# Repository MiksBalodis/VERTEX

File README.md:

# VERTEX Flight Computer

Avionics system for actively controlled high-power rockets: an STM32 flight computer that estimates vehicle state in real time and drives control actuators, plus a ground station for receiving, storing and analysing flight data.

**Authors:** Miks Balodis, Aleksandrs Jesiļevskis

---

## Overview

The system covers the full avionics chain:

- **Flight computer** – sensor acquisition, state estimation, active control and flight data logging
- **Telemetry link** – LoRa downlink to the ground during flight
- **Ground station** – receiver hardware and a desktop GUI for live visualisation and data export

The flight computer can:

- estimate the rocket's attitude, velocity and altitude in real time,
- drive up to **4 PWM actuator channels** (servo-actuated control fins or a TVC gimbal),
- log flight data on board for post-flight analysis,
- stream telemetry to the ground station during flight.

## What is active control?

Active control continuously:

1. measures the vehicle's state (orientation, angular rates, velocity),
2. computes the required correction,
3. commands the actuators via PWM.

Unlike passive stabilisation, which relies on fixed aerodynamic surfaces, an active system can respond to disturbances such as wind gusts, thrust misalignment and asymmetries during flight.

## Architecture

## Hardware

| Function | Component | Notes |
|---|---|---|
| MCU | STM32F405RGT6 | Cortex-M4F, FPU + DSP, DMA for peripheral transfers |
| Barometer | BMP388 | Altitude estimation; SPI up to 10 MHz |
| IMU | LSM6DSO | 3-axis accelerometer + gyroscope|
| GNSS | u-blox MAX-M10S | ~1.5 m CEP position accuracy, high altitude capable |
| Flight data storage | SPI NOR flash | Exposed to a PC as a USB Mass Storage device |
| Configuration storage | 24LC64 EEPROM | Persistent parameters, separate from flight logs |
| Telemetry | EBYTE E22-400M22S | LoRa operating at 433 MHz |
| Actuators | 4× PWM outputs | Servo driven fins or TVC gimbal |

Flight logs and configuration are deliberately kept on separate memories: the EEPROM is simple to access and keeps configuration safe from being overwritten by logging.

## Software

- **Firmware:** C/C++ on STM32 (STM32CubeIDE / STM32Cube HAL), DMA-driven sensor I/O
- **State estimation:** Kalman filter
- **Control:** PID controller
- **Simulation & tuning:** MATLAB/Simulink for controller and filter design; RocketPy for flight trajectory simulation
- **Ground station GUI:** JavaScript + Svelte, with real time plots and data export
- **PCB design:** KiCad

## Intended users

- student and university rocketry teams
- embedded systems and control algorithm developers
- experimental rocketry and UAV hobbyists

## Deliverables

- Flight computer PCB
- Flight firmware
- Ground station hardware and GUI
- Documentation

## License

All materials in this repository are free to use. Attribution is not required, but a short mention of where they came from is appreciated.

## Contact

For questions, contact Miks Balodis.

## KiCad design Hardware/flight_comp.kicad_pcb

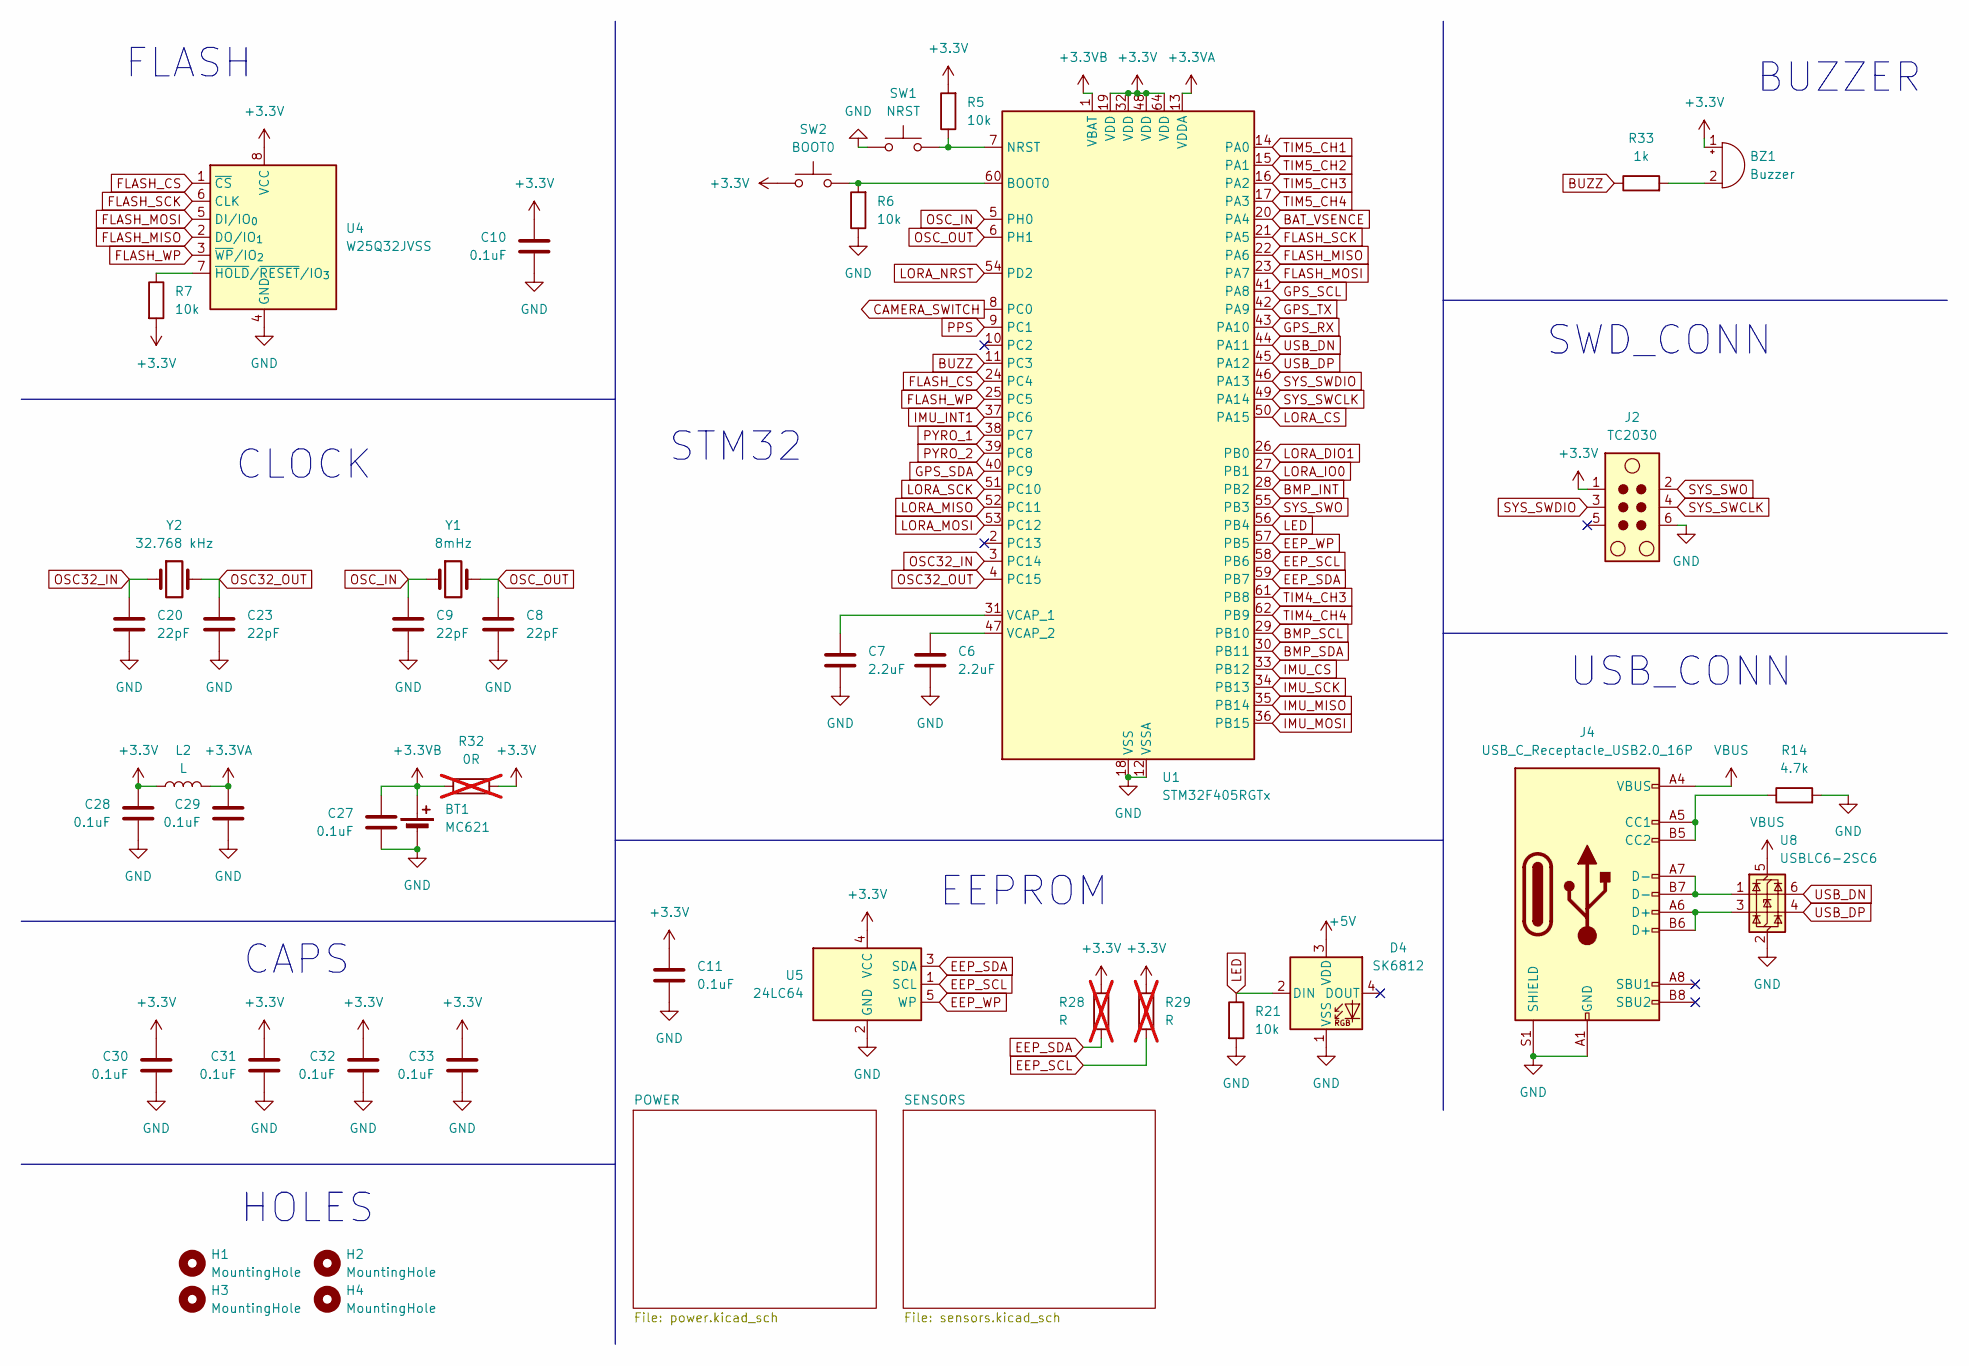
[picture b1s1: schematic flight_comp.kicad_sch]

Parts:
BT1: MC621; BatteryHolder_Keystone_2998_1x6.8mm
BZ1: Buzzer; Buzzer_CUI_CPT-9019S-SMT
C6, C7: 2.2uF; C_0603_1608Metric
C8, C9: 22pF; C_0603_1608Metric
C10, C11, C27, C28, C29, C30, C31, C32, C33: 0.1uF; C_0603_1608Metric
C20, C23: 22pF; C_0402_1005Metric
D4: SK6812; LED_SK6812_PLCC4_5.0x5.0mm_P3.2mm
H1, H2, H3, H4: MountingHole; MountingHole_3.2mm_M3
J2: TC2030; Tag-Connect_TC2030-IDC-NL_2x03_P1.27mm_Vertical
J4: USB_C_Receptacle_USB2.0_16P; USB_C_Receptacle_GCT_USB4110
L2: L; L_0603_1608Metric
R5, R6, R7, R21: 10k; R_0603_1608Metric
R14: 4.7k; R_0603_1608Metric
R28, R29: R; R_0603_1608Metric; not fitted
R32: 0R; R_0603_1608Metric; not fitted
R33: 1k; R_0603_1608Metric
SW1: NRST; SW_SPST_CK_RS282G05A3
SW2: BOOT0; SW_SPST_CK_RS282G05A3
U1: STM32F405RGTx; LQFP-64_10x10mm_P0.5mm
U4: W25Q32JVSS; SOIC-8_5.3x5.3mm_P1.27mm
U5: 24LC64; SOT-23-5
U8: USBLC6-2SC6; SOT-23-6
Y1: 8mHz; Crystal_SMD_5032-2Pin_5.0x3.2mm
Y2: 32.768 kHz; Crystal_SMD_3215-2Pin_3.2x1.5mm

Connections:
+3.3V: BZ1.1 (+), C10.1, C11.1, C28.1, C30.1, C31.1, C32.1, C33.1, J2.1, L2.1, R5.2, R7.2, R28.1, R29.1, R32.2, SW2.1, U1.19 (VDD), U1.32 (VDD), U1.48 (VDD), U1.64 (VDD), U4.8 (VCC), U5.4 (VCC); also elsewhere on the board
+3.3VA: C29.1, L2.2, U1.13 (VDDA)
+3.3VB: BT1.1 (+), C27.1, R32.1, U1.1 (VBAT)
+5V: D4.3 (VDD); also elsewhere on the board
BAT_VSENCE: U1.20 (PA4); also elsewhere on the board
BMP_INT: U1.28 (PB2); also elsewhere on the board
BMP_SCL: U1.29 (PB10); also elsewhere on the board
BMP_SDA: U1.30 (PB11); also elsewhere on the board
BUZZ: R33.1, U1.11 (PC3)
CAMERA_SWITCH: U1.8 (PC0); also elsewhere on the board
EEP_SCL: R29.2, U1.58 (PB6), U5.1 (SCL)
EEP_SDA: R28.2, U1.59 (PB7), U5.3 (SDA)
EEP_WP: U1.57 (PB5), U5.5 (WP)
FLASH_CS: U1.24 (PC4), U4.1 (~CS)
FLASH_MISO: U1.22 (PA6), U4.2 (DO/IO_{1})
FLASH_MOSI: U1.23 (PA7), U4.5 (DI/IO_{0})
FLASH_SCK: U1.21 (PA5), U4.6 (CLK)
FLASH_WP: U1.25 (PC5), U4.3 (~WP/IO_{2})
GND: BT1.2 (-), C6.2, C7.2, C8.2, C9.2, C10.2, C11.2, C20.2, C23.2, C27.2, C28.2, C29.2, C30.2, C31.2, C32.2, C33.2, D4.1 (VSS), J2.6, J4.A1 (GND), J4.A12 (GND), J4.B1 (GND), J4.B12 (GND), J4.S1 (SHIELD), R6.1, R14.2, R21.2, SW1.1, U1.12 (VSSA), U1.18 (VSS), U1.63 (VSS), U4.4 (GND), U5.2 (GND), U8.2 (GND); also elsewhere on the board
GPS_RX: U1.43 (PA10); also elsewhere on the board
GPS_SCL: U1.41 (PA8); also elsewhere on the board
GPS_SDA: U1.40 (PC9); also elsewhere on the board
GPS_TX: U1.42 (PA9); also elsewhere on the board
IMU_CS: U1.33 (PB12); also elsewhere on the board
IMU_INT1: U1.37 (PC6); also elsewhere on the board
IMU_MISO: U1.35 (PB14); also elsewhere on the board
IMU_MOSI: U1.36 (PB15); also elsewhere on the board
IMU_SCK: U1.34 (PB13); also elsewhere on the board
LED: D4.2 (DIN), R21.1, U1.56 (PB4)
LORA_CS: U1.50 (PA15); also elsewhere on the board
LORA_DIO1: U1.26 (PB0); also elsewhere on the board
LORA_IO0: U1.27 (PB1); also elsewhere on the board
LORA_MISO: U1.52 (PC11); also elsewhere on the board
LORA_MOSI: U1.53 (PC12); also elsewhere on the board
LORA_NRST: U1.54 (PD2); also elsewhere on the board
LORA_SCK: U1.51 (PC10); also elsewhere on the board
unnamed: BZ1.2 (-), R33.2
unnamed: J4.A5 (CC1), J4.B5 (CC2), R14.1
unnamed: J4.A6 (D+), J4.B6 (D+), U8.3 (I/O2)
unnamed: J4.A7 (D-), J4.B7 (D-), U8.1 (I/O1)
unnamed: R6.2, SW2.2, U1.60 (BOOT0)
unnamed: R5.1, SW1.2, U1.7 (NRST)
unnamed: C7.1, U1.31 (VCAP_1)
unnamed: C6.1, U1.47 (VCAP_2)
unnamed: R7.1, U4.7 (~HOLD/~RESET/IO_{3})
OSC32_IN: C20.1, U1.3 (PC14), Y2.1
OSC32_OUT: C23.1, U1.4 (PC15), Y2.2
OSC_IN: C9.1, U1.5 (PH0), Y1.1
OSC_OUT: C8.1, U1.6 (PH1), Y1.2
PPS: U1.9 (PC1); also elsewhere on the board
PYRO_1: U1.38 (PC7); also elsewhere on the board
PYRO_2: U1.39 (PC8); also elsewhere on the board
SYS_SWCLK: J2.4, U1.49 (PA14)
SYS_SWDIO: J2.3, U1.46 (PA13)
SYS_SWO: J2.2, U1.55 (PB3)
TIM4_CH3: U1.61 (PB8); also elsewhere on the board
TIM4_CH4: U1.62 (PB9); also elsewhere on the board
TIM5_CH1: U1.14 (PA0); also elsewhere on the board
TIM5_CH2: U1.15 (PA1); also elsewhere on the board
TIM5_CH3: U1.16 (PA2); also elsewhere on the board
TIM5_CH4: U1.17 (PA3); also elsewhere on the board
USB_DN: U1.44 (PA11), U8.6 (I/O1)
USB_DP: U1.45 (PA12), U8.4 (I/O2)
VBUS: J4.A4 (VBUS), J4.A9 (VBUS), J4.B4 (VBUS), J4.B9 (VBUS), U8.5 (VBUS); also elsewhere on the board

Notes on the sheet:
CAPS
CLOCK
BUZZER
USB_CONN
EEPROM
STM32
SWD_CONN
HOLES
FLASH

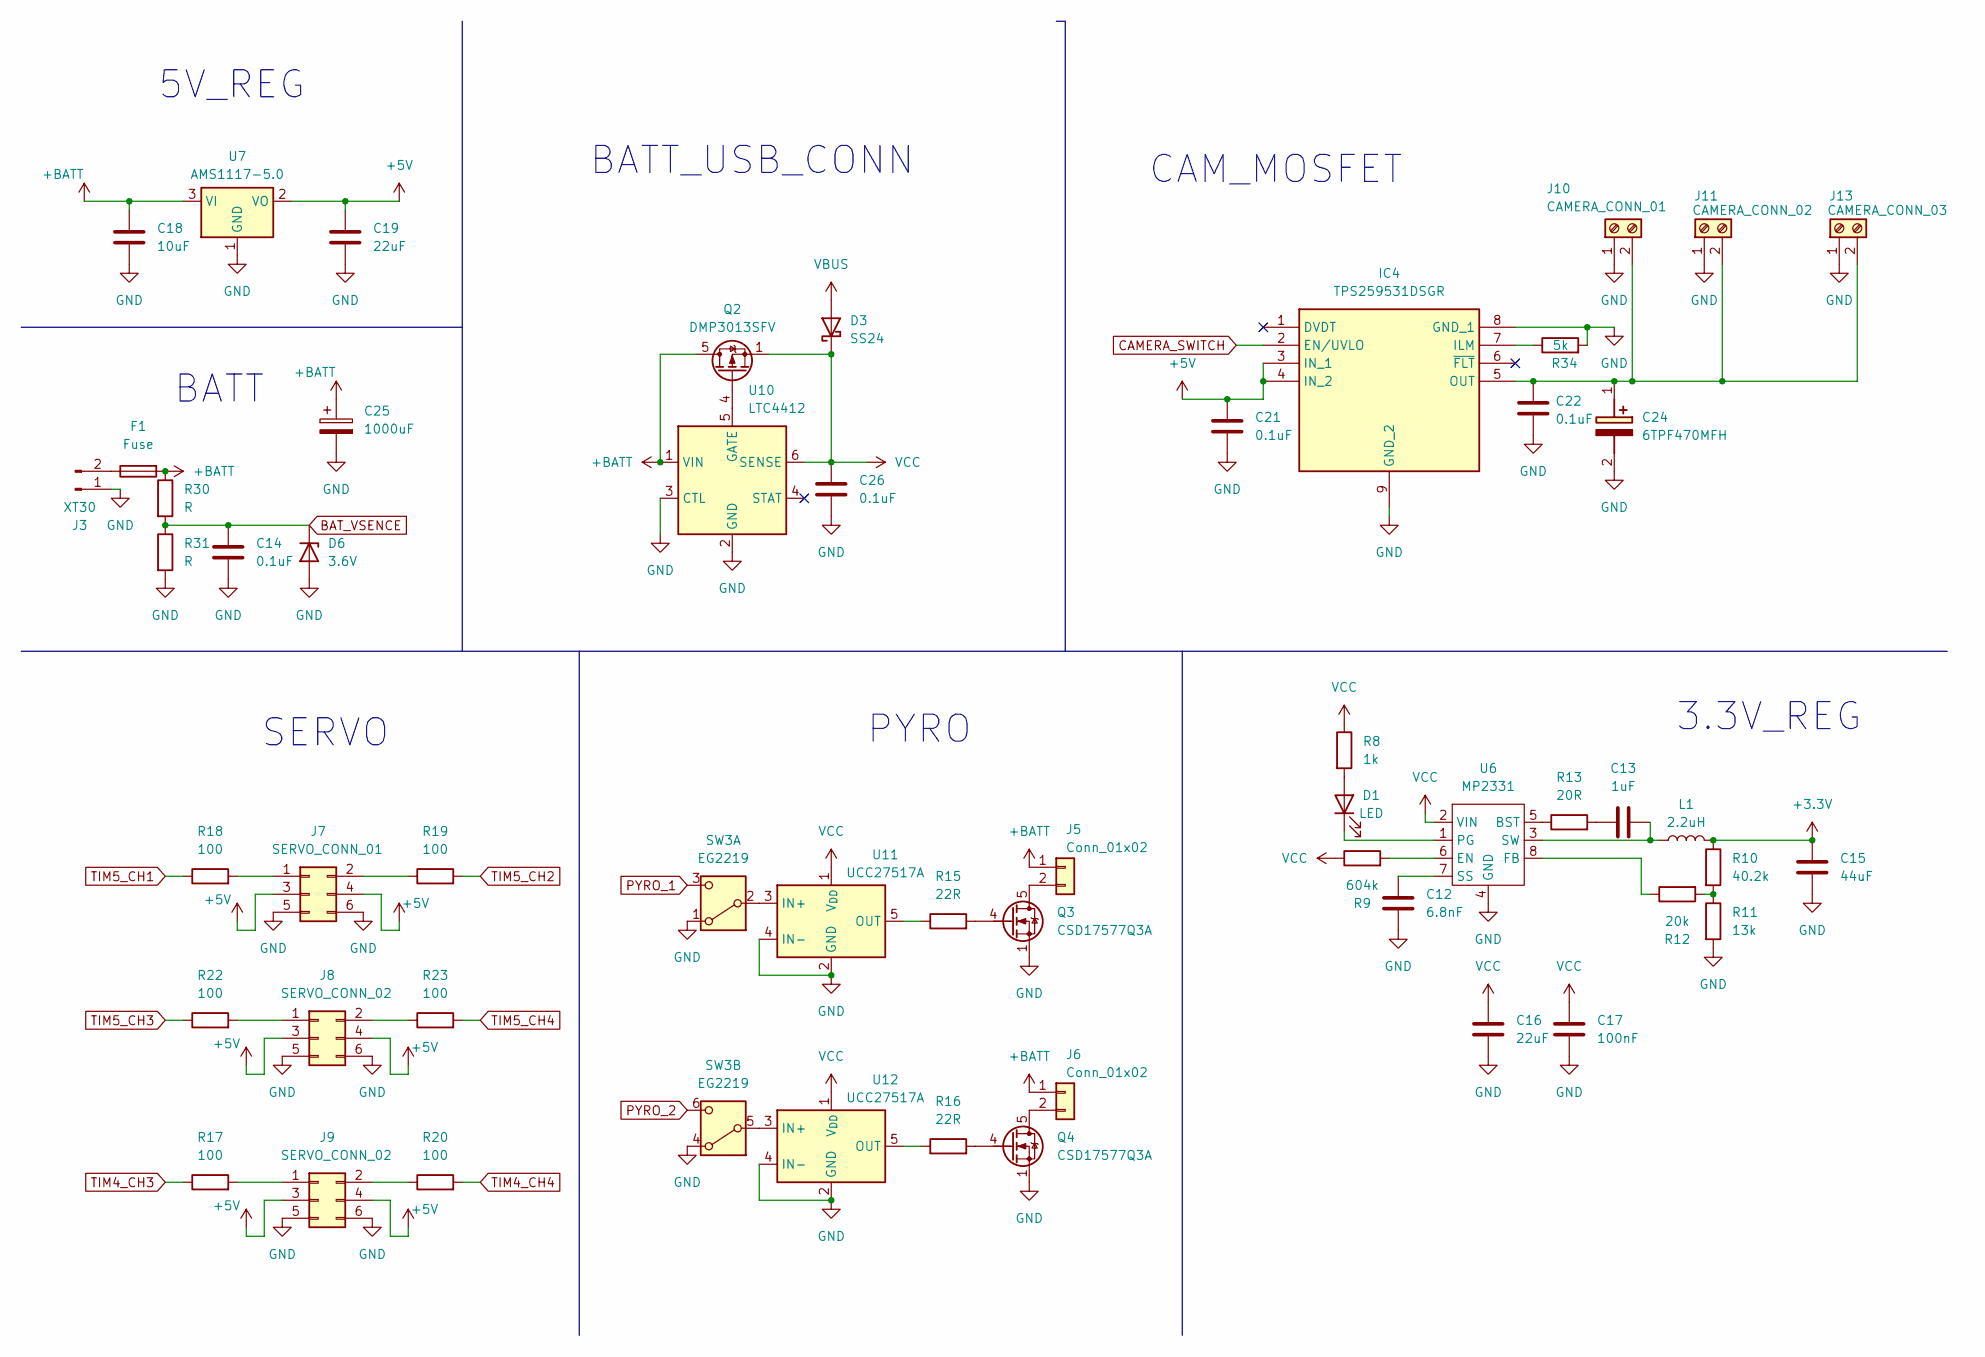
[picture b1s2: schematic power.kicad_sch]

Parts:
C12: 6.8nF; C_0603_1608Metric
C13: 1uF; C_0603_1608Metric
C14, C26: 0.1uF; C_0603_1608Metric
C15: 44uF; C_0805_2012Metric
C16: 22uF; C_0805_2012Metric
C17: 100nF; C_0603_1608Metric
C18: 10uF; C_0603_1608Metric
C19: 22uF; C_0603_1608Metric
C21, C22: 0.1uF; C_0402_1005Metric; MPN C0402C104K4RAC7411
C24: 6TPF470MFH; CP_EIA-3216-10_Kemet-I; Mouser Part Number 667-6TPF470MFH
C25: 1000uF; CP_Axial_L10.0mm_D6.0mm_P15.00mm_Horizontal
D1: LED; LED_0603_1608Metric
D3: SS24; D_SMA
D6: 3.6V; D_SOD-128
F1: Fuse; Fuse_1206_3216Metric
IC4: TPS259531DSGR; WSON-8-1EP_2x2mm_P0.5mm_EP0.9x1.6mm_ThermalVias; Mouser Part Number 595-TPS259531DSGR
J3: XT30; AMASS_XT30PW-M_1x02_P2.50mm_Horizontal
J5, J6: Conn_01x02; TerminalBlock_4Ucon_1x02_P3.50mm_Vertical; MPN 284514-2
J7: SERVO_CONN_01; PinHeader_2x03_P2.54mm_Vertical; MPN 90131-0763
J8, J9: SERVO_CONN_02; PinHeader_2x03_P2.54mm_Vertical; MPN 90131-0763
J10: CAMERA_CONN_01; TerminalBlock_Xinya_XY308-2.54-2P_1x02_P2.54mm_Horizontal; MPN 284514-2
J11: CAMERA_CONN_02; TerminalBlock_Xinya_XY308-2.54-2P_1x02_P2.54mm_Horizontal; MPN 284514-2
J13: CAMERA_CONN_03; TerminalBlock_Xinya_XY308-2.54-2P_1x02_P2.54mm_Horizontal; MPN 284514-2
L1: 2.2uH; L_6.3x6.3_H3
Q2: DMP3013SFV; Diodes_PowerDI3333-8
Q3, Q4: CSD17577Q3A; VSON-8_3.3x3.3mm_P0.65mm_NexFET
R8: 1k; R_0603_1608Metric
R9: 604k; R_0603_1608Metric
R10: 40.2k; R_0603_1608Metric
R11: 13k; R_0603_1608Metric
R12: 20k; R_0603_1608Metric
R13: 20R; R_0603_1608Metric
R15, R16: 22R; R_0603_1608Metric
R17, R19, R20, R22, R23: 100; R_0402_1005Metric; MPN RC1206FR-07100RL
R18: 100; R_0402_1005Metric
R30, R31: R; R_0603_1608Metric
R34: 5k; R_0402_1005Metric; MPN RC0402FR-075K76L
SW3: EG2219; SW_DPDT_CK_JS202011JCQN
U6: MP2331; SOT-583-8
U7: AMS1117-5.0; SOT-223-3_TabPin2
U10: LTC4412; TSOT-23-6
U11, U12: UCC27517A; SOT-23-5

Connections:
+3.3V: C15.1, L1.2, R10.1; also elsewhere on the board
+5V: C19.1, C21.1, IC4.3 (IN_1), IC4.4 (IN_2), J7.3, J7.4, J8.3, J8.4, J9.3, J9.4, U7.2 (VO); also elsewhere on the board
+BATT: C18.1, C25.1, F1.2, J5.1, J6.1, Q2.5 (D), R30.1, U7.3 (VI), U10.1 (VIN)
BAT_VSENCE: C14.1, D6.1 (K), R30.2, R31.1; also elsewhere on the board
CAMERA_SWITCH: IC4.2 (EN/UVLO); also elsewhere on the board
GND: C12.2, C14.2, C15.2, C16.2, C17.2, C18.2, C19.2, C21.2, C22.2, C24.2 (-), C25.2, C26.2, D6.2 (A), IC4.8 (GND_1), IC4.9 (GND_2), J3.1, J7.5, J7.6, J8.5, J8.6, J9.5, J9.6, J10.1, J11.1, J13.1, Q3.1 (S), Q3.2 (S), Q3.3 (S), Q4.1 (S), Q4.2 (S), Q4.3 (S), R11.2, R31.2, R34.2, SW3.1 (A), SW3.4 (A), U6.4 (GND), U7.1 (GND), U10.2 (GND), U10.3 (CTL), U11.2 (GND), U11.4 (IN-), U12.2 (GND), U12.4 (IN-); also elsewhere on the board
unnamed: C13.1, R13.2
unnamed: C22.1, C24.1 (+), IC4.5 (OUT), J10.2, J11.2, J13.2
unnamed: D1.2 (A), R8.2
unnamed: D1.1 (K), U6.1 (PG)
unnamed: IC4.7 (ILM), R34.1
unnamed: F1.1, J3.2
unnamed: J5.2, Q3.5 (D)
unnamed: J6.2, Q4.5 (D)
unnamed: J7.1, R18.2
unnamed: J7.2, R19.1
unnamed: J8.1, R22.2
unnamed: J8.2, R23.1
unnamed: J9.1, R17.2
unnamed: J9.2, R20.1
unnamed: Q2.4 (G), U10.5 (GATE)
unnamed: Q3.4 (G), R15.2
unnamed: Q4.4 (G), R16.2
unnamed: R10.2, R11.1, R12.2
unnamed: SW3.2 (B), U11.3 (IN+)
unnamed: SW3.5 (B), U12.3 (IN+)
unnamed: R13.1, U6.5 (BST)
unnamed: R9.2, U6.6 (EN)
unnamed: R12.1, U6.8 (FB)
unnamed: C12.1, U6.7 (SS)
unnamed: C13.2, L1.1, U6.3 (SW)
unnamed: R15.1, U11.5 (OUT)
unnamed: R16.1, U12.5 (OUT)
PYRO_1: SW3.3 (C); also elsewhere on the board
PYRO_2: SW3.6 (C); also elsewhere on the board
TIM4_CH3: R17.1; also elsewhere on the board
TIM4_CH4: R20.2; also elsewhere on the board
TIM5_CH1: R18.1; also elsewhere on the board
TIM5_CH2: R19.2; also elsewhere on the board
TIM5_CH3: R22.1; also elsewhere on the board
TIM5_CH4: R23.2; also elsewhere on the board
VBUS: D3.2 (A); also elsewhere on the board
VCC: C16.1, C17.1, C26.1, D3.1 (K), Q2.1 (S), Q2.2 (S), Q2.3 (S), R8.1, R9.1, U6.2 (VIN), U10.6 (SENSE), U11.1 (V_{DD}), U12.1 (V_{DD})

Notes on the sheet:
SERVO
PYRO
BATT_USB_CONN
5V_REG
3.3V_REG
BATT
CAM_MOSFET

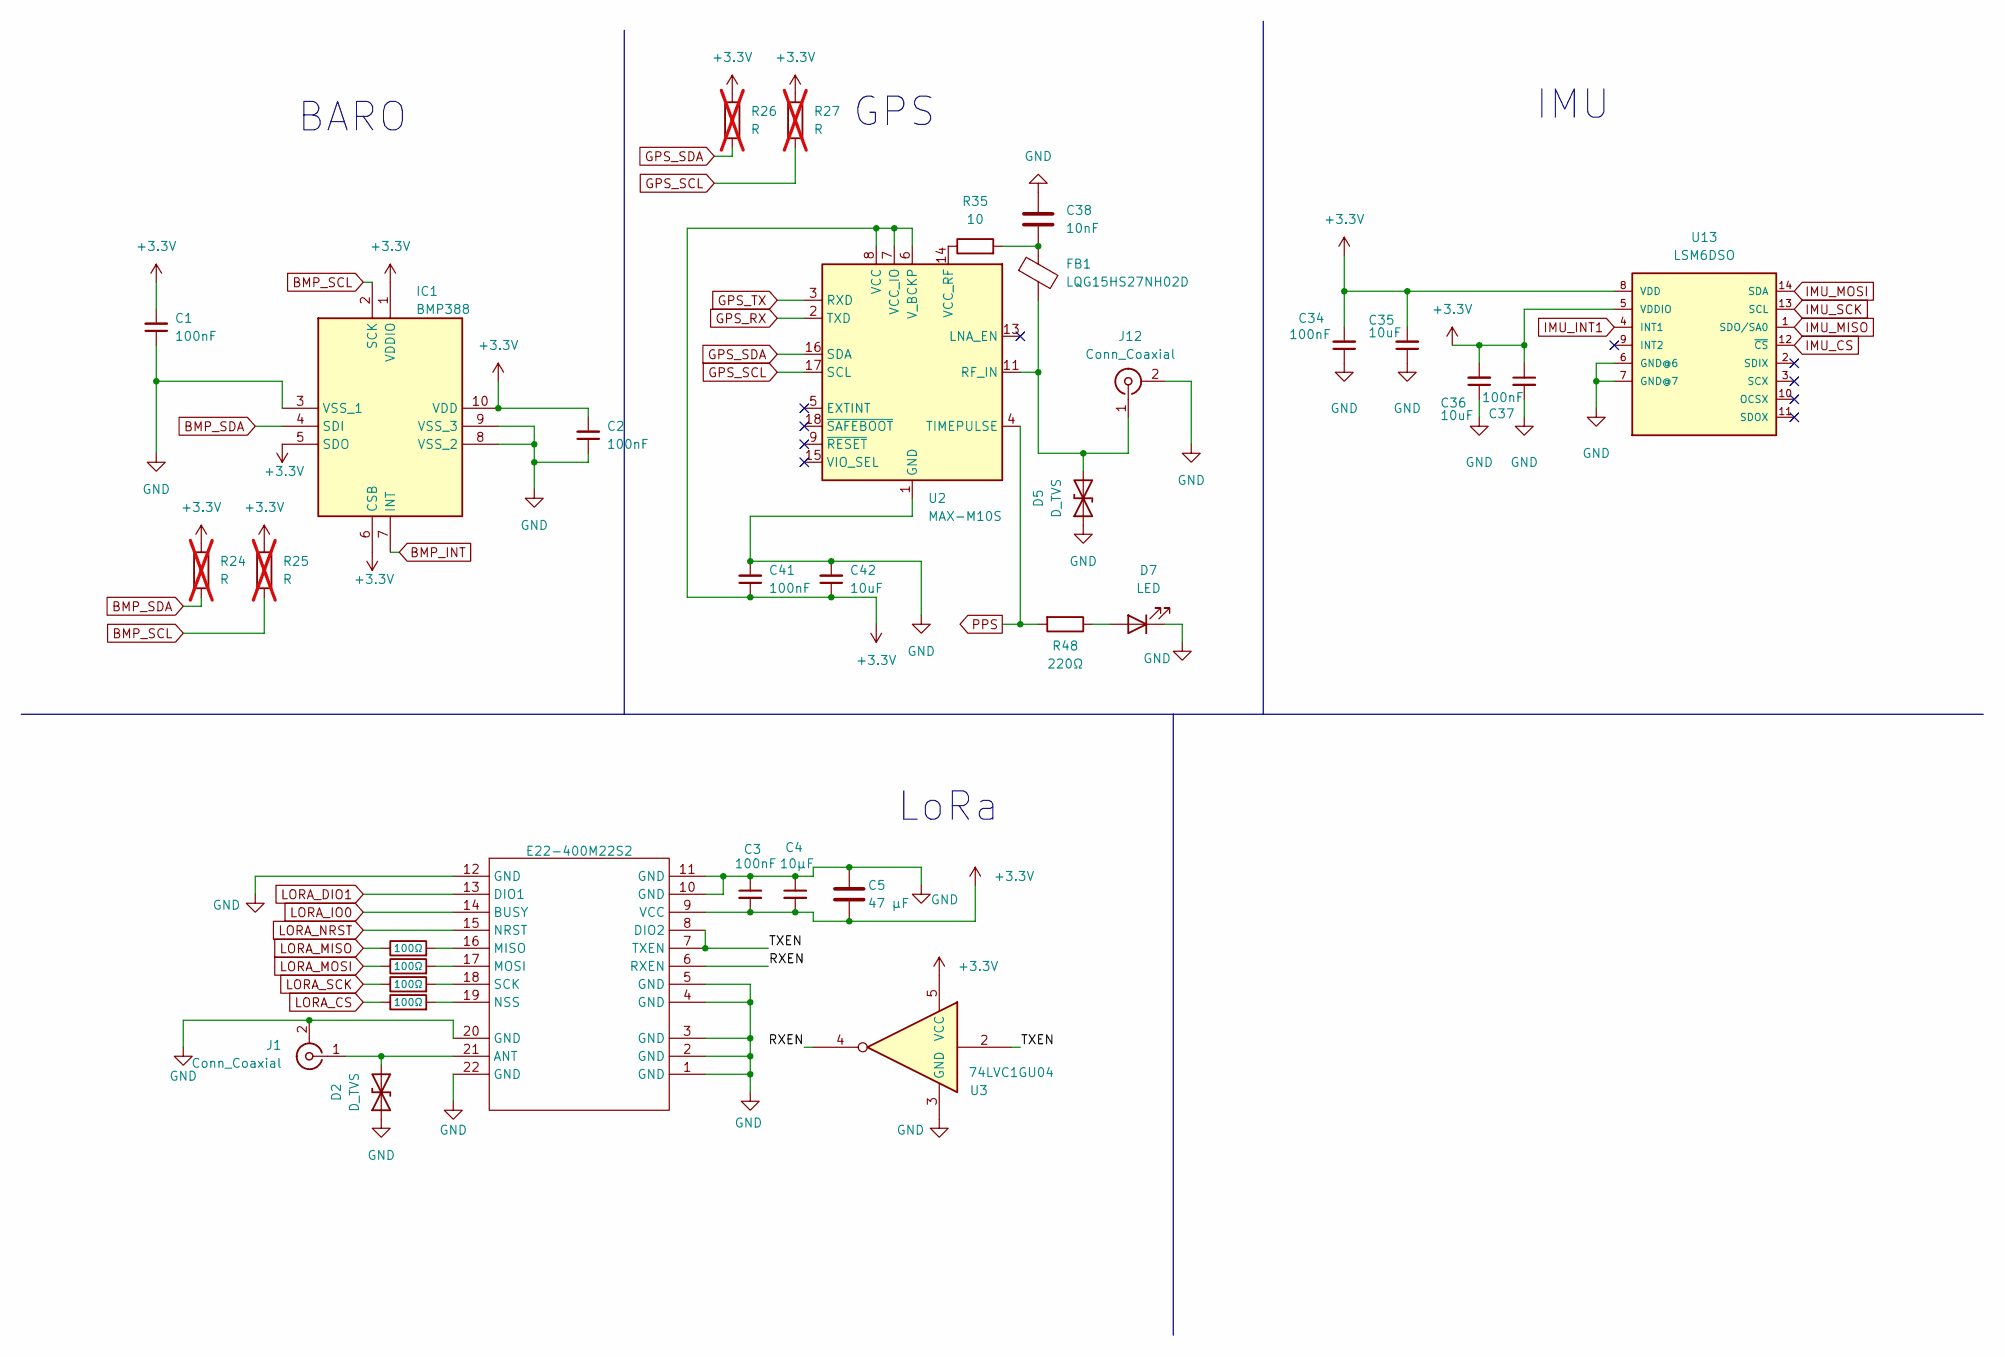
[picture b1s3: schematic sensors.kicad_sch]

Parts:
C1, C2, C3, C41: 100nF; C_0402_1005Metric
C4: 10µF; C_0402_1005Metric
C5: 47 µF; C_1206_3216Metric
C34, C37: 100nF; C_0402_1005Metric; MPN C0402C104K4RAC7411
C35, C36: 10uF; C_0402_1005Metric; MPN C0402C106M9PACTU
C38: 10nF; C_0603_1608Metric
C42: 10uF; C_0603_1608Metric
D2, D5: D_TVS; D_SOD-523
D7: LED; LED_0603_1608Metric
E22-400M22S2: E22-400M22S
FB1: LQG15HS27NH02D; L_0402_1005Metric
IC1: BMP388; ST_HLGA-10_2x2mm_P0.5mm_LayoutBorder3x2y; Manufacturer_Part_Number BMP388
J1, J12: Conn_Coaxial; SMA_Molex_73251-2200_Horizontal
R1, R2, R3, R4: 100Ω; R_0402_1005Metric
R24, R25, R26, R27: R; R_0603_1608Metric; not fitted
R35: 10; R_0603_1608Metric
R48: 220Ω; R_0402_1005Metric
U2: MAX-M10S; ublox_MAX
U3: 74LVC1GU04; SOT-23-5
U13: LSM6DSO; LGA-14_3x2.5mm_P0.5mm_LayoutBorder3x4y; MPN LSM6DSOTR

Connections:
+3.3V: C1.2, C2.2, C3.2, C4.2, C5.2, C34.2, C35.2, C36.2, C37.1, C41.1, C42.1, E22-400M22S2.9 (VCC), IC1.1 (VDDIO), IC1.5 (SDO), IC1.6 (CSB), IC1.10 (VDD), R24.1, R25.1, R26.1, R27.1, U2.6 (V_BCKP), U2.7 (VCC_IO), U2.8 (VCC), U3.5 (VCC), U13.5 (VDDIO), U13.8 (VDD); also elsewhere on the board
/SENSORS/RXEN: E22-400M22S2.6 (RXEN), U3.4
/SENSORS/TXEN: E22-400M22S2.7 (TXEN), E22-400M22S2.8 (DIO2), U3.2
BMP_INT: IC1.7 (INT); also elsewhere on the board
BMP_SCL: IC1.2 (SCK), R25.2; also elsewhere on the board
BMP_SDA: IC1.4 (SDI), R24.2; also elsewhere on the board
GND: C1.1, C2.1, C3.1, C4.1, C5.1, C34.1, C35.1, C36.1, C37.2, C38.2, C41.2, C42.2, D2.1 (A1), D5.1 (A1), D7.1 (K), E22-400M22S2.1 (GND), E22-400M22S2.2 (GND), E22-400M22S2.3 (GND), E22-400M22S2.4 (GND), E22-400M22S2.5 (GND), E22-400M22S2.10 (GND), E22-400M22S2.11 (GND), E22-400M22S2.12 (GND), E22-400M22S2.20 (GND), E22-400M22S2.22 (GND), IC1.3 (VSS_1), IC1.8 (VSS_2), IC1.9 (VSS_3), J1.2 (Ext), J12.2 (Ext), U2.1 (GND), U2.10 (GND), U2.12 (GND), U3.3 (GND), U13.6 (GND@6), U13.7 (GND@7); also elsewhere on the board
GPS_RX: U2.2 (TXD); also elsewhere on the board
GPS_SCL: R27.2, U2.17 (SCL); also elsewhere on the board
GPS_SDA: R26.2, U2.16 (SDA); also elsewhere on the board
GPS_TX: U2.3 (RXD); also elsewhere on the board
IMU_CS: U13.12 (~CS); also elsewhere on the board
IMU_INT1: U13.4 (INT1); also elsewhere on the board
IMU_MISO: U13.1 (SDO/SA0); also elsewhere on the board
IMU_MOSI: U13.14 (SDA); also elsewhere on the board
IMU_SCK: U13.13 (SCL); also elsewhere on the board
LORA_CS: R4.1; also elsewhere on the board
LORA_DIO1: E22-400M22S2.13 (DIO1); also elsewhere on the board
LORA_IO0: E22-400M22S2.14 (BUSY); also elsewhere on the board
LORA_MISO: R1.1; also elsewhere on the board
LORA_MOSI: R2.1; also elsewhere on the board
LORA_NRST: E22-400M22S2.15 (NRST); also elsewhere on the board
LORA_SCK: R3.1; also elsewhere on the board
unnamed: C38.1, FB1.1, R35.2
unnamed: D2.2 (A2), E22-400M22S2.21 (ANT), J1.1 (In)
unnamed: D5.2 (A2), FB1.2, J12.1 (In), U2.11 (RF_IN)
unnamed: D7.2 (A), R48.1
unnamed: E22-400M22S2.16 (MISO), R1.2
unnamed: E22-400M22S2.17 (MOSI), R2.2
unnamed: E22-400M22S2.19 (NSS), R4.2
unnamed: E22-400M22S2.18 (SCK), R3.2
unnamed: R35.1, U2.14 (VCC_RF)
PPS: R48.2, U2.4 (TIMEPULSE); also elsewhere on the board

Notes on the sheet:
GPS
IMU
LoRa
BARO

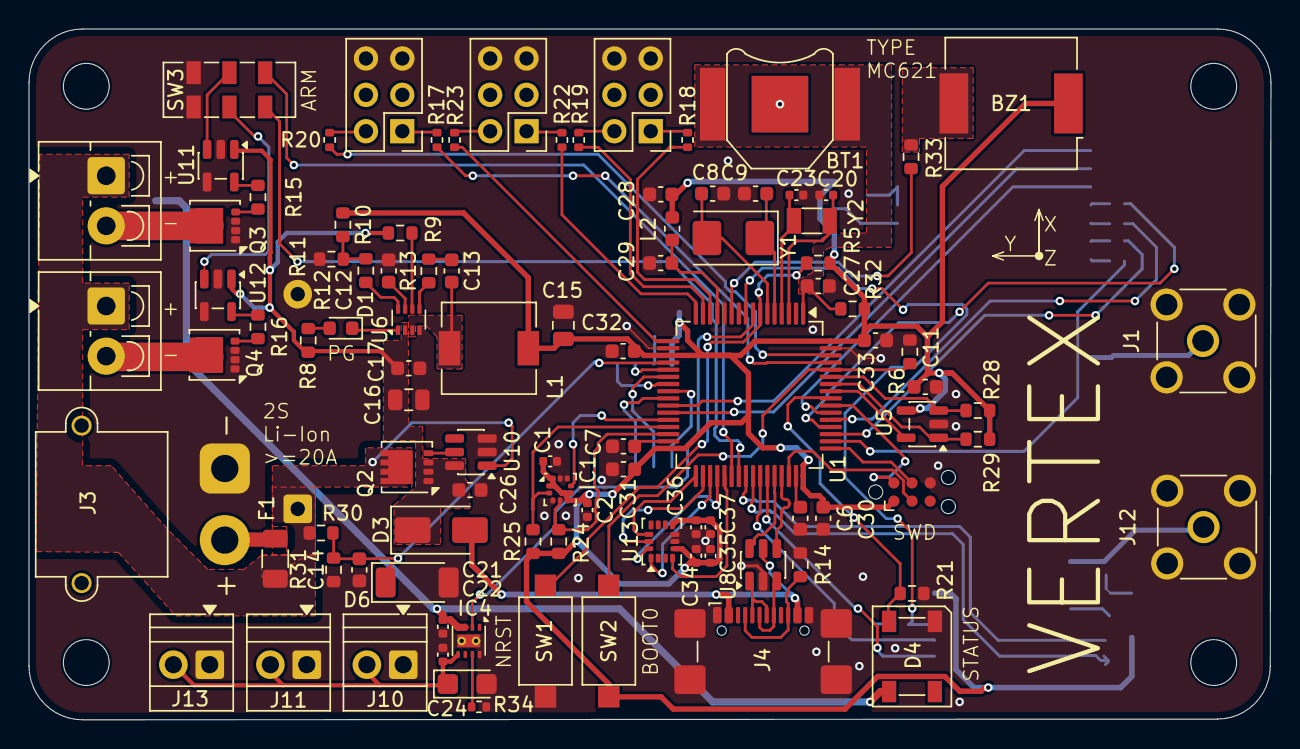
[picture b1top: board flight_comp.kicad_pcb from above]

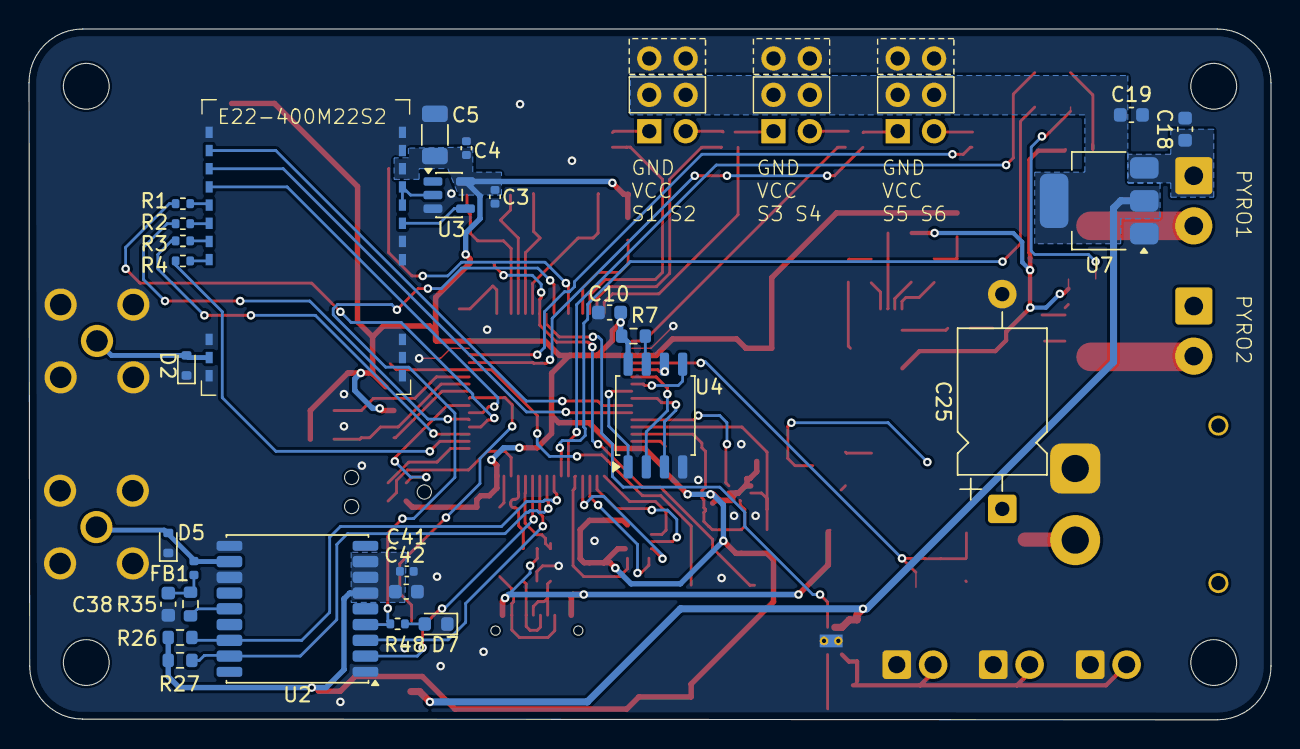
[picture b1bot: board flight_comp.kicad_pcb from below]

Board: 4 copper layers, 86.7 x 48.2 mm, 129 parts (28 on the bottom side), 104 nets.

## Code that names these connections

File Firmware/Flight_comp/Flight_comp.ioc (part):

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Mcu.Name=STM32F405RGTx
Mcu.Package=LQFP64
Mcu.UserName=STM32F405RGTx
PA0-WKUP.GPIOParameters=GPIO_Label
PA0-WKUP.GPIO_Label=SERVO1
PA0-WKUP.Signal=S_TIM5_CH1
PA1.GPIOParameters=GPIO_Label
PA1.GPIO_Label=SERVO2
PA1.Signal=S_TIM5_CH2
PA10.GPIOParameters=GPIO_Label
PA10.GPIO_Label=GPS_RX
PA10.Mode=Asynchronous
PA10.Signal=USART1_RX
PA11.Mode=Device_Only
PA11.Signal=USB_OTG_FS_DM
PA12.Mode=Device_Only
PA12.Signal=USB_OTG_FS_DP
PA13.Mode=Serial_Wire
PA13.Signal=SYS_JTMS-SWDIO
PA14.Mode=Serial_Wire
PA14.Signal=SYS_JTCK-SWCLK
PA15.GPIOParameters=GPIO_Speed,PinState,GPIO_Label
PA15.GPIO_Label=LORA_NSS
PA15.GPIO_Speed=GPIO_SPEED_FREQ_VERY_HIGH
PA15.PinState=GPIO_PIN_SET
PA15.Signal=GPIO_Output
PA2.GPIOParameters=GPIO_Label
PA2.GPIO_Label=SERVO3
PA2.Signal=S_TIM5_CH3
PA3.GPIOParameters=GPIO_Label
PA3.GPIO_Label=SERVO4
PA3.Signal=S_TIM5_CH4
PA4.GPIOParameters=GPIO_Label
PA4.GPIO_Label=BAT_VSENCE
PA4.Signal=ADCx_IN4
PA5.GPIOParameters=GPIO_Label
PA5.GPIO_Label=FLASH_SCK
PA5.Mode=Full_Duplex_Master
PA5.Signal=SPI1_SCK
PA6.GPIOParameters=GPIO_Label
PA6.GPIO_Label=FLASH_MISO
PA6.Mode=Full_Duplex_Master
PA6.Signal=SPI1_MISO
PA7.GPIOParameters=GPIO_Label
PA7.GPIO_Label=FLASH_MOSI
PA7.Mode=Full_Duplex_Master
PA7.Signal=SPI1_MOSI
PA8.GPIOParameters=GPIO_Label,GPIO_Pu
PA8.GPIO_Label=GPS_SCL
PA8.GPIO_Pu=GPIO_PULLUP
PA8.Mode=I2C
PA8.Signal=I2C3_SCL
PA9.GPIOParameters=GPIO_Label
PA9.GPIO_Label=GPS_TX
PA9.Mode=Asynchronous
PA9.Signal=USART1_TX
PB0.GPIOParameters=GPIO_PuPd,GPIO_Label
PB0.GPIO_Label=LORA_DIO1
PB0.GPIO_PuPd=GPIO_PULLDOWN
PB0.Signal=GPXTI0
PB1.GPIOParameters=GPIO_PuPd,GPIO_Label
PB1.GPIO_Label=LORA_IO0
PB1.GPIO_PuPd=GPIO_PULLDOWN
PB1.Signal=GPIO_Input
PB10.GPIOParameters=GPIO_Label,GPIO_Pu
PB10.GPIO_Label=BMP_SCL
PB10.GPIO_Pu=GPIO_PULLUP
PB10.Mode=I2C
PB10.Signal=I2C2_SCL
PB11.GPIOParameters=GPIO_Label,GPIO_Pu
PB11.GPIO_Label=BMP_SDA
PB11.GPIO_Pu=GPIO_PULLUP
PB11.Mode=I2C
PB11.Signal=I2C2_SDA
PB12.GPIOParameters=GPIO_Speed,PinState,GPIO_Label
PB12.GPIO_Label=IMU_NSS
PB12.GPIO_Speed=GPIO_SPEED_FREQ_VERY_HIGH
PB12.PinState=GPIO_PIN_SET
PB12.Signal=GPIO_Output
PB13.GPIOParameters=GPIO_Label
PB13.GPIO_Label=IMU_SCK
PB13.Mode=Full_Duplex_Master
PB13.Signal=SPI2_SCK
PB14.GPIOParameters=GPIO_Label
PB14.GPIO_Label=IMU_MISO
PB14.Mode=Full_Duplex_Master
PB14.Signal=SPI2_MISO
PB15.GPIOParameters=GPIO_Label
PB15.GPIO_Label=IMU_MOSI
PB15.Mode=Full_Duplex_Master
PB15.Signal=SPI2_MOSI
PB2.GPIOParameters=GPIO_Label
PB2.GPIO_Label=BMP_INT
PB2.Signal=GPXTI2
PB3.GPIOParameters=GPIO_Label
PB3.GPIO_Label=LED
PB3.Signal=S_TIM2_CH2
PB4.Signal=GPIO_Analog
PB5.GPIOParameters=GPIO_Speed,PinState,GPIO_Label
PB5.GPIO_Label=EEP_WP
PB5.GPIO_Speed=GPIO_SPEED_FREQ_VERY_HIGH
PB5.PinState=GPIO_PIN_RESET
PB5.Signal=GPIO_Output
PB6.GPIOParameters=GPIO_Label,GPIO_Pu
PB6.GPIO_Label=EEP_SCL
PB6.GPIO_Pu=GPIO_PULLUP
PB6.Mode=I2C
PB6.Signal=I2C1_SCL
PB7.GPIOParameters=GPIO_Label,GPIO_Pu
PB7.GPIO_Label=EEP_SDA
PB7.GPIO_Pu=GPIO_PULLUP
PB7.Mode=I2C
PB7.Signal=I2C1_SDA
PB8.GPIOParameters=GPIO_Label
PB8.GPIO_Label=SERVO5
PB8.Signal=S_TIM4_CH3
PB9.GPIOParameters=GPIO_Label
PB9.GPIO_Label=SERVO6
PB9.Signal=S_TIM4_CH4
PC0.GPIOParameters=GPIO_Label
PC0.GPIO_Label=CAM_CTRL
PC0.Signal=GPIO_Output
PC10.GPIOParameters=GPIO_Label
PC10.GPIO_Label=LORA_SCK
PC10.Mode=Full_Duplex_Master
PC10.Signal=SPI3_SCK
PC11.GPIOParameters=GPIO_Label
PC11.GPIO_Label=LORA-MISO
PC11.Mode=Full_Duplex_Master
PC11.Signal=SPI3_MISO
PC12.GPIOParameters=GPIO_Label
PC12.GPIO_Label=LORA_MOSI
PC12.Mode=Full_Duplex_Master
PC12.Signal=SPI3_MOSI
PC14-OSC32_IN.Mode=LSE-External-Oscillator
PC14-OSC32_IN.Signal=RCC_OSC32_IN
PC15-OSC32_OUT.Mode=LSE-External-Oscillator
PC15-OSC32_OUT.Signal=RCC_OSC32_OUT
PC3.GPIOParameters=GPIO_Label
PC3.GPIO_Label=BUZZER
PC3.Signal=GPIO_Output
PC4.GPIOParameters=GPIO_Speed,PinState,GPIO_Label
PC4.GPIO_Label=FLASH_NSS
PC4.GPIO_Speed=GPIO_SPEED_FREQ_VERY_HIGH
PC4.PinState=GPIO_PIN_SET
PC4.Signal=GPIO_Output
PC5.GPIOParameters=GPIO_Speed,PinState,GPIO_Label
PC5.GPIO_Label=FLASH_WP
PC5.GPIO_Speed=GPIO_SPEED_FREQ_VERY_HIGH
PC5.PinState=GPIO_PIN_SET
PC5.Signal=GPIO_Output
PC6.GPIOParameters=GPIO_Label,GPIO_ModeDefaultEXTI
PC6.GPIO_Label=IMU_INT1
PC6.GPIO_ModeDefaultEXTI=GPIO_MODE_IT_RISING
PC6.Signal=GPXTI6
PC7.GPIOParameters=GPIO_Label
PC7.GPIO_Label=PYRO1
PC7.Signal=GPIO_Output
PC8.GPIOParameters=GPIO_Label
PC8.GPIO_Label=PYRO2
PC8.Signal=GPIO_Output
PC9.GPIOParameters=GPIO_Label,GPIO_Pu
PC9.GPIO_Label=GPS_SDA
PC9.GPIO_Pu=GPIO_PULLUP
PC9.Mode=I2C
PC9.Signal=I2C3_SDA
PD2.GPIOParameters=PinState,GPIO_Label
PD2.GPIO_Label=LORA_NRST
PD2.PinState=GPIO_PIN_SET
PD2.Signal=GPIO_Output
PH0-OSC_IN.Mode=HSE-External-Oscillator
PH0-OSC_IN.Signal=RCC_OSC_IN
PH1-OSC_OUT.Mode=HSE-External-Oscillator
PH1-OSC_OUT.Signal=RCC_OSC_OUT
RCC.HSE_VALUE=8000000
RCC.SYSCLKFreq_VALUE=144000000
RCC.SYSCLKSource=RCC_SYSCLKSOURCE_PLLCLK
board=custom

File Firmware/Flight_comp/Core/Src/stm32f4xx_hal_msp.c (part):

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
    __HAL_RCC_GPIOA_CLK_ENABLE();
    /**ADC1 GPIO Configuration
    PA4     ------> ADC1_IN4
    */
    GPIO_InitStruct.Pin = BAT_VSENCE_Pin;
    GPIO_InitStruct.Mode = GPIO_MODE_ANALOG;
    GPIO_InitStruct.Pull = GPIO_NOPULL;
    HAL_GPIO_Init(BAT_VSENCE_GPIO_Port, &GPIO_InitStruct);

    /* ADC1 DMA Init */
    /* ADC1 Init */
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    __HAL_RCC_ADC1_CLK_DISABLE();

    /**ADC1 GPIO Configuration
    PA4     ------> ADC1_IN4
    */
    HAL_GPIO_DeInit(BAT_VSENCE_GPIO_Port, BAT_VSENCE_Pin);

    /* ADC1 DMA DeInit */
    HAL_DMA_DeInit(hadc->DMA_Handle);
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
    __HAL_RCC_GPIOB_CLK_ENABLE();
    /**I2C1 GPIO Configuration
    PB6     ------> I2C1_SCL
    PB7     ------> I2C1_SDA
    */
    GPIO_InitStruct.Pin = EEP_SCL_Pin|EEP_SDA_Pin;
    GPIO_InitStruct.Mode = GPIO_MODE_AF_OD;
    GPIO_InitStruct.Pull = GPIO_PULLUP;
    GPIO_InitStruct.Speed = GPIO_SPEED_FREQ_VERY_HIGH;
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
    __HAL_RCC_GPIOB_CLK_ENABLE();
    /**I2C2 GPIO Configuration
    PB10     ------> I2C2_SCL
    PB11     ------> I2C2_SDA
    */
    GPIO_InitStruct.Pin = BMP_SCL_Pin|BMP_SDA_Pin;
    GPIO_InitStruct.Mode = GPIO_MODE_AF_OD;
    GPIO_InitStruct.Pull = GPIO_PULLUP;
    GPIO_InitStruct.Speed = GPIO_SPEED_FREQ_VERY_HIGH;
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    __HAL_RCC_GPIOC_CLK_ENABLE();
    __HAL_RCC_GPIOA_CLK_ENABLE();
    /**I2C3 GPIO Configuration
    PC9     ------> I2C3_SDA
    PA8     ------> I2C3_SCL
    */
    GPIO_InitStruct.Pin = GPS_SDA_Pin;
    GPIO_InitStruct.Mode = GPIO_MODE_AF_OD;
    GPIO_InitStruct.Pull = GPIO_PULLUP;
    GPIO_InitStruct.Speed = GPIO_SPEED_FREQ_VERY_HIGH;
    GPIO_InitStruct.Alternate = GPIO_AF4_I2C3;
    HAL_GPIO_Init(GPS_SDA_GPIO_Port, &GPIO_InitStruct);

    GPIO_InitStruct.Pin = GPS_SCL_Pin;
    GPIO_InitStruct.Mode = GPIO_MODE_AF_OD;
    GPIO_InitStruct.Pull = GPIO_PULLUP;
    GPIO_InitStruct.Speed = GPIO_SPEED_FREQ_VERY_HIGH;
    GPIO_InitStruct.Alternate = GPIO_AF4_I2C3;
    HAL_GPIO_Init(GPS_SCL_GPIO_Port, &GPIO_InitStruct);

    /* Peripheral clock enable */
    __HAL_RCC_I2C3_CLK_ENABLE();
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    __HAL_RCC_I2C1_CLK_DISABLE();

    /**I2C1 GPIO Configuration
    PB6     ------> I2C1_SCL
    PB7     ------> I2C1_SDA
    */
    HAL_GPIO_DeInit(EEP_SCL_GPIO_Port, EEP_SCL_Pin);

    HAL_GPIO_DeInit(EEP_SDA_GPIO_Port, EEP_SDA_Pin);

    /* USER CODE BEGIN I2C1_MspDeInit 1 */

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    __HAL_RCC_I2C2_CLK_DISABLE();

    /**I2C2 GPIO Configuration
    PB10     ------> I2C2_SCL
    PB11     ------> I2C2_SDA
    */
    HAL_GPIO_DeInit(BMP_SCL_GPIO_Port, BMP_SCL_Pin);

    HAL_GPIO_DeInit(BMP_SDA_GPIO_Port, BMP_SDA_Pin);

    /* USER CODE BEGIN I2C2_MspDeInit 1 */

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    __HAL_RCC_I2C3_CLK_DISABLE();

    /**I2C3 GPIO Configuration
    PC9     ------> I2C3_SDA
    PA8     ------> I2C3_SCL
    */
    HAL_GPIO_DeInit(GPS_SDA_GPIO_Port, GPS_SDA_Pin);

    HAL_GPIO_DeInit(GPS_SCL_GPIO_Port, GPS_SCL_Pin);

    /* USER CODE BEGIN I2C3_MspDeInit 1 */

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
    __HAL_RCC_GPIOA_CLK_ENABLE();
    /**SPI1 GPIO Configuration
    PA5     ------> SPI1_SCK
    PA6     ------> SPI1_MISO
    PA7     ------> SPI1_MOSI
    */
    GPIO_InitStruct.Pin = FLASH_SCK_Pin|FLASH_MISO_Pin|FLASH_MOSI_Pin;
    GPIO_InitStruct.Mode = GPIO_MODE_AF_PP;
    GPIO_InitStruct.Pull = GPIO_NOPULL;
    GPIO_InitStruct.Speed = GPIO_SPEED_FREQ_VERY_HIGH;
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
    __HAL_RCC_GPIOB_CLK_ENABLE();
    /**SPI2 GPIO Configuration
    PB13     ------> SPI2_SCK
    PB14     ------> SPI2_MISO
    PB15     ------> SPI2_MOSI
    */
    GPIO_InitStruct.Pin = IMU_SCK_Pin|IMU_MISO_Pin|IMU_MOSI_Pin;
    GPIO_InitStruct.Mode = GPIO_MODE_AF_PP;
    GPIO_InitStruct.Pull = GPIO_NOPULL;
    GPIO_InitStruct.Speed = GPIO_SPEED_FREQ_VERY_HIGH;
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
    __HAL_RCC_GPIOC_CLK_ENABLE();
    /**SPI3 GPIO Configuration
    PC10     ------> SPI3_SCK
    PC11     ------> SPI3_MISO
    PC12     ------> SPI3_MOSI
    */
    GPIO_InitStruct.Pin = LORA_SCK_Pin|LORA_MISO_Pin|LORA_MOSI_Pin;
    GPIO_InitStruct.Mode = GPIO_MODE_AF_PP;
    GPIO_InitStruct.Pull = GPIO_NOPULL;
    GPIO_InitStruct.Speed = GPIO_SPEED_FREQ_VERY_HIGH;
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    __HAL_RCC_SPI1_CLK_DISABLE();

    /**SPI1 GPIO Configuration
    PA5     ------> SPI1_SCK
    PA6     ------> SPI1_MISO
    PA7     ------> SPI1_MOSI
    */
    HAL_GPIO_DeInit(GPIOA, FLASH_SCK_Pin|FLASH_MISO_Pin|FLASH_MOSI_Pin);

    /* USER CODE BEGIN SPI1_MspDeInit 1 */

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    __HAL_RCC_SPI2_CLK_DISABLE();

    /**SPI2 GPIO Configuration
    PB13     ------> SPI2_SCK
    PB14     ------> SPI2_MISO
    PB15     ------> SPI2_MOSI
    */
    HAL_GPIO_DeInit(GPIOB, IMU_SCK_Pin|IMU_MISO_Pin|IMU_MOSI_Pin);

    /* SPI2 DMA DeInit */
    HAL_DMA_DeInit(hspi->hdmarx);
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    __HAL_RCC_SPI3_CLK_DISABLE();

    /**SPI3 GPIO Configuration
    PC10     ------> SPI3_SCK
    PC11     ------> SPI3_MISO
    PC12     ------> SPI3_MOSI
    */
    HAL_GPIO_DeInit(GPIOC, LORA_SCK_Pin|LORA_MISO_Pin|LORA_MOSI_Pin);

    /* SPI3 interrupt DeInit */
    HAL_NVIC_DisableIRQ(SPI3_IRQn);
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    /* USER CODE END TIM2_MspPostInit 0 */
    __HAL_RCC_GPIOB_CLK_ENABLE();
    /**TIM2 GPIO Configuration
    PB3     ------> TIM2_CH2
    */
    GPIO_InitStruct.Pin = LED_Pin;
    GPIO_InitStruct.Mode = GPIO_MODE_AF_PP;
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
    __HAL_RCC_GPIOB_CLK_ENABLE();
    /**TIM4 GPIO Configuration
    PB8     ------> TIM4_CH3
    PB9     ------> TIM4_CH4
    */
    GPIO_InitStruct.Pin = SERVO5_Pin|SERVO6_Pin;
    GPIO_InitStruct.Mode = GPIO_MODE_AF_PP;
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
    __HAL_RCC_GPIOA_CLK_ENABLE();
    /**TIM5 GPIO Configuration
    PA0-WKUP     ------> TIM5_CH1
    PA1     ------> TIM5_CH2
    PA2     ------> TIM5_CH3
    PA3     ------> TIM5_CH4
    */
    GPIO_InitStruct.Pin = SERVO1_Pin|SERVO2_Pin|SERVO3_Pin|SERVO4_Pin;
    GPIO_InitStruct.Mode = GPIO_MODE_AF_PP;
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
    __HAL_RCC_GPIOA_CLK_ENABLE();
    /**USART1 GPIO Configuration
    PA9     ------> USART1_TX
    PA10     ------> USART1_RX
    */
    GPIO_InitStruct.Pin = GPS_TX_Pin|GPS_RX_Pin;
    GPIO_InitStruct.Mode = GPIO_MODE_AF_PP;
    GPIO_InitStruct.Pull = GPIO_NOPULL;
    GPIO_InitStruct.Speed = GPIO_SPEED_FREQ_VERY_HIGH;
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    __HAL_RCC_USART1_CLK_DISABLE();

    /**USART1 GPIO Configuration
    PA9     ------> USART1_TX
    PA10     ------> USART1_RX
    */
    HAL_GPIO_DeInit(GPIOA, GPS_TX_Pin|GPS_RX_Pin);

    /* USART1 DMA DeInit */
    HAL_DMA_DeInit(huart->hdmarx);
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
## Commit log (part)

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2025-12-03 Sensors added
2025-12-17 Power sch added
2025-12-20 Changes in power system
2025-12-23 Minor changes in sensors and peripherals
2025-12-25 5V removed, PCB routing
2026-01-07 schem uzlabojumi
2026-01-09 Kondensators
2026-01-12 Drivers #1
2026-01-27 Drivers #2
2026-01-27 Include errors fixed
2026-01-27 env removed
2026-01-28 USB MSD setup
2026-01-29 Create ...
2026-01-29 BMP388 test code
2026-01-30 EEPROM read and write test
2026-01-30 Servo driver
2026-02-01 Debug LED driver
2026-03-13 Ground station mock-up
2026-03-19 GUI testing ready
2026-03-19 added IMU filtering
2026-03-20 test files and docker added
2026-03-20 non-blocking buzzer implementation
2026-03-20 Small changes in IMU driver
2026-03-23 readme testing updated
2026-03-31 USB MSC
2026-03-31 Fast write and 8 MB chip
2026-04-01 FatFS, named constants
2026-04-03 GPS antenna connections, pps is connected to the mcu, pps diode replaced
2026-04-12 stm32wb55 BLE support for ground station, DMA requests for IMU, LED moved to PB3
2026-04-14 adding testing
2026-04-14 testing
2026-04-14 Testing readded
2026-04-14 LoRa and USB for ground station, telemetry package
2026-04-15 Altitude calculation and telemetry
2026-04-15 init functions for peripherals
2026-04-15 some additional changes
2026-04-15 Printable altitude telemetry with us timestamps
2026-04-15 Integration of gyro
2026-04-16 gyro integration now in dps instead of mpds
2026-04-18 Telemetry is now displayed in the GUI
2026-04-20 Status LED now shows faults, added timeout to lora driver
2026-04-21 Servo for TVC
2026-04-30 Quaternion for imy gyro
2026-05-03 gui update
2026-05-05 axis fixed
2026-05-12 sensor filtering added
2026-06-08 pid added
2026-06-08 pid values upadted

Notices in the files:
Firmware/Flight_comp/Core/Src/stm32f4xx_hal_msp.c:
Copyright (c) 2026 STMicroelectronics.
All rights reserved.
This software is licensed under terms that can be found in the LICENSE file
